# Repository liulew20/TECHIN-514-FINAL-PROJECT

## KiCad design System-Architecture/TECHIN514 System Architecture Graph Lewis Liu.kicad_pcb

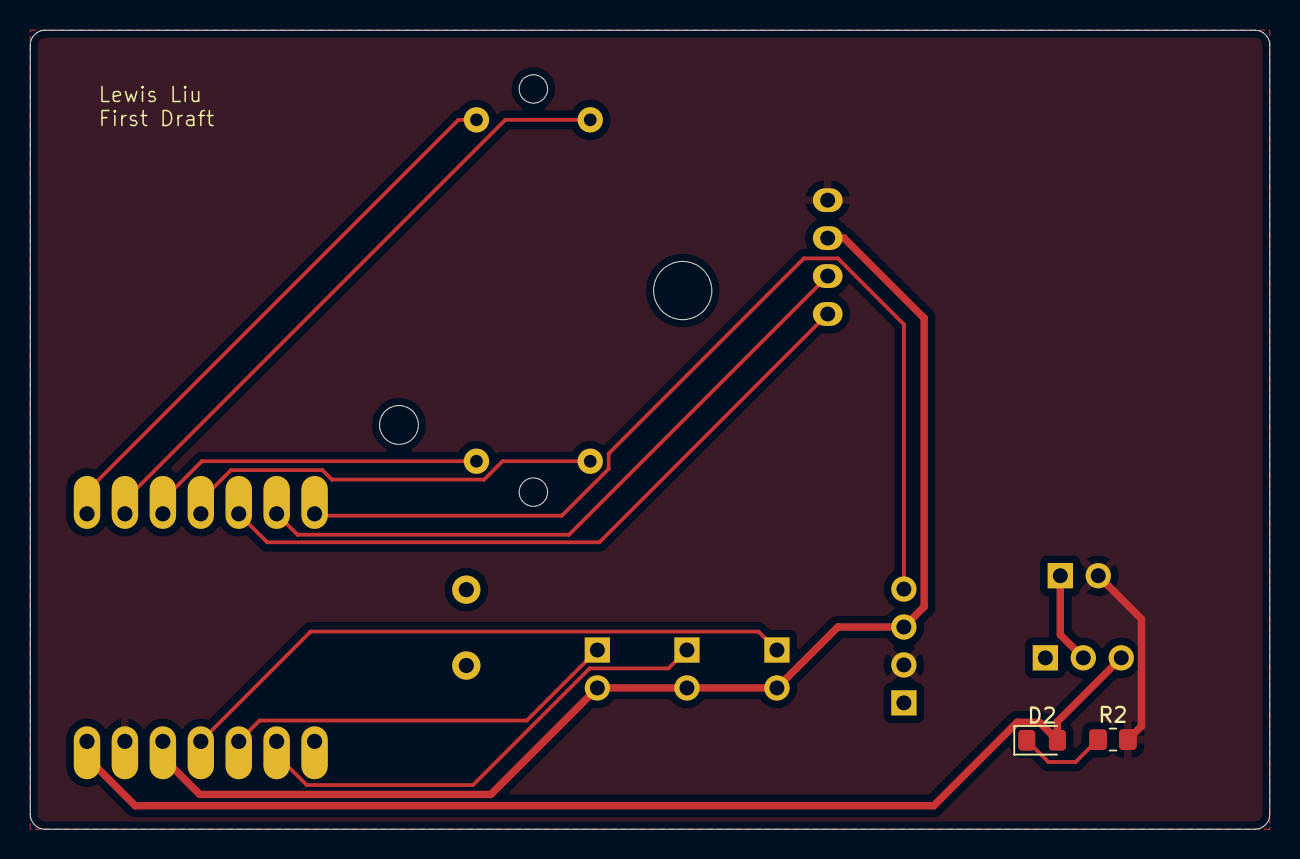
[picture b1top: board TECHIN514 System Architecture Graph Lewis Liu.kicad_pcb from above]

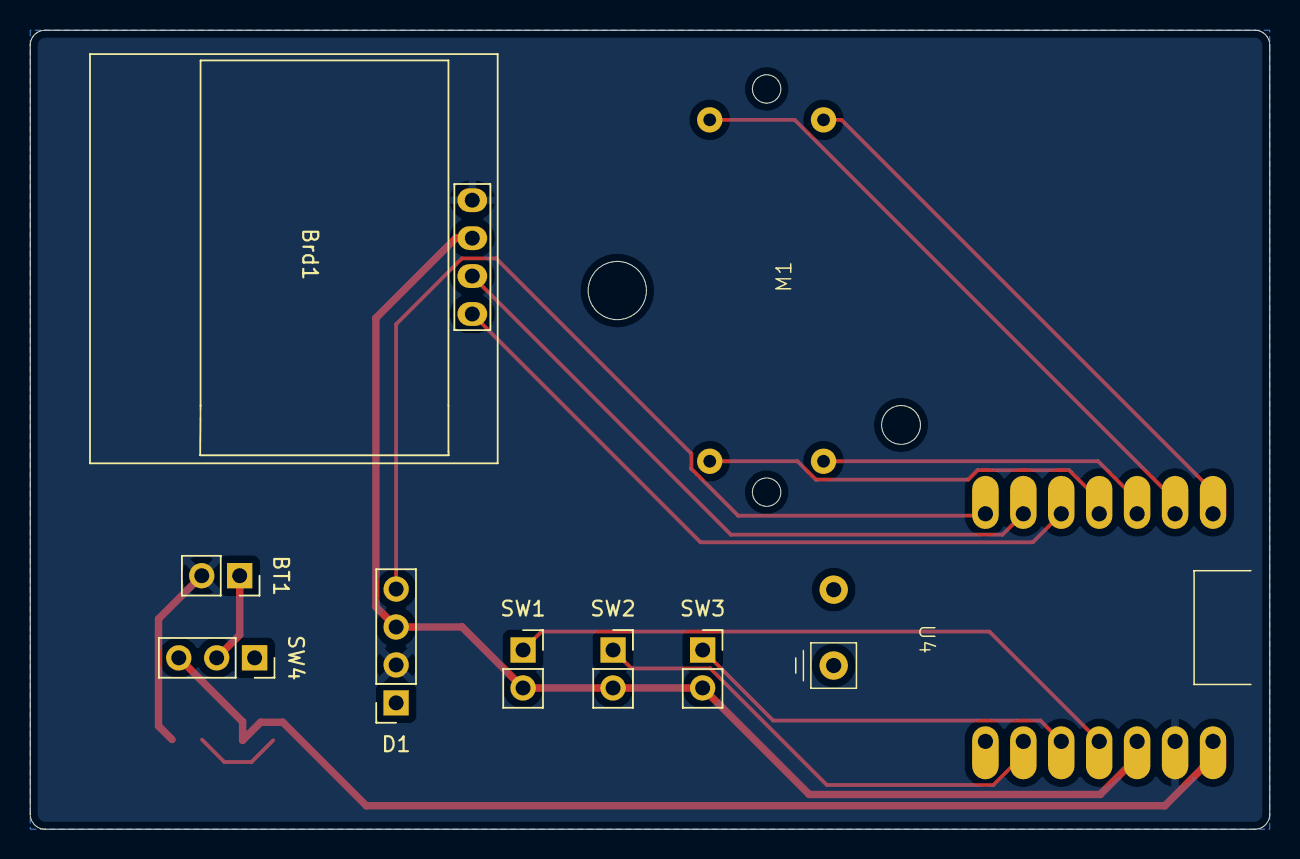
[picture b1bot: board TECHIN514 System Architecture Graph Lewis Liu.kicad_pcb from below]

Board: 2 copper layers, 83.0 x 53.5 mm, 11 parts (9 on the bottom side), 15 nets.

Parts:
BT1: Battery_Cell; PinSocket_1x02_P2.54mm_Vertical
Brd1: SSD1306; 128x64OLED
D1: NeoPixel_THT; PinSocket_1x04_P2.54mm_Vertical
D2: LED; LED_0805_2012Metric_Pad1.15x1.40mm_HandSolder
M1: Stepper_Motor_bipolar; x27_stepper
R2: 85ohm; R_0805_2012Metric_Pad1.20x1.40mm_HandSolder
SW1, SW2, SW3: SW_Push; PinSocket_1x02_P2.54mm_Vertical
SW4: SW_SPDT; PinSocket_1x03_P2.54mm_Vertical
U4: Xiaoesp32c3; XIAO_ESP32

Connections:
+3.3V: Brd1.2 (VCC), D1.3 (VDD), SW1.2, SW2.2, SW3.2, U4.12 (3V3)
/BAT: BT1.1 (+), SW4.2 (B)
/VCC: D2.2 (A), SW4.3 (C), U4.14 (5V)
GND: BT1.2 (-), Brd1.1 (GND), D1.2 (GND), R2.2, U4.13 (GND)
unnamed: Brd1.3 (SCL), U4.6 (GPIO6_A5_D5_SCL)
unnamed: Brd1.4 (SDA), U4.5 (GPIO4_A3_D3_SDA)
unnamed: D1.4 (DIN), U4.7 (GPIO43_TX_D6)
unnamed: D2.1 (K), R2.1
unnamed: M1.2 (-), U4.1 (GPIO1_A0_D0)
unnamed: M1.1, U4.2 (GPIO2_A1_D1)
unnamed: M1.3, U4.3 (GPIO3_A2_D2)
unnamed: M1.4, U4.4 (GPIO4_A3_D3)
unnamed: SW2.1, U4.9 (GPIO7_A8_D8_SCK)
unnamed: SW3.1, U4.10 (GPIO8_A9_D9_CIPO)
unnamed: SW1.1, U4.11 (GPIO9_A10_D10_COPI)

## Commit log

2026-01-27 update system architecture
2026-02-09 update battery life
